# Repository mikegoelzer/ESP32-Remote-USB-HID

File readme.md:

# USB HID Keyboard over Wifi

This project is the hardware and firmware for an ESP32-based remote USB keyboard. It's a dongle that plugs into a USB port on a computer and sends keystrokes that it receives over Wifi.  The connector `J3` also allows for wiring up to the PC motherboard's `F_PANEL` control pins, allowing for remote on/off and remote reboot.  

If you run a JST 4-conductor wire to `F_PANEL` there is a small adapter PCB that plugs it into the motherboard connector.

## Hardware

There are two Kicad projects, one for the USB key and one for the small adapter PCB:

  - USB keyboard PCB
    - [Schematic](Schematics/USBHIDKey.pdf)
    - [`USBHIDKey`](USBHIDKey/)
  - Adapter PCB
    - [Schematic](Schematics/F_PANEL_Shim.pdf)
    - [`F_PANEL_Adapter`](F_PANEL_Adapter/)

## Firmware

The firmware is in the [`esp32-firmware`](esp32-firmware/) directory. See its [README](esp32-firmware/usb-hid-kybd/README.md) for details.

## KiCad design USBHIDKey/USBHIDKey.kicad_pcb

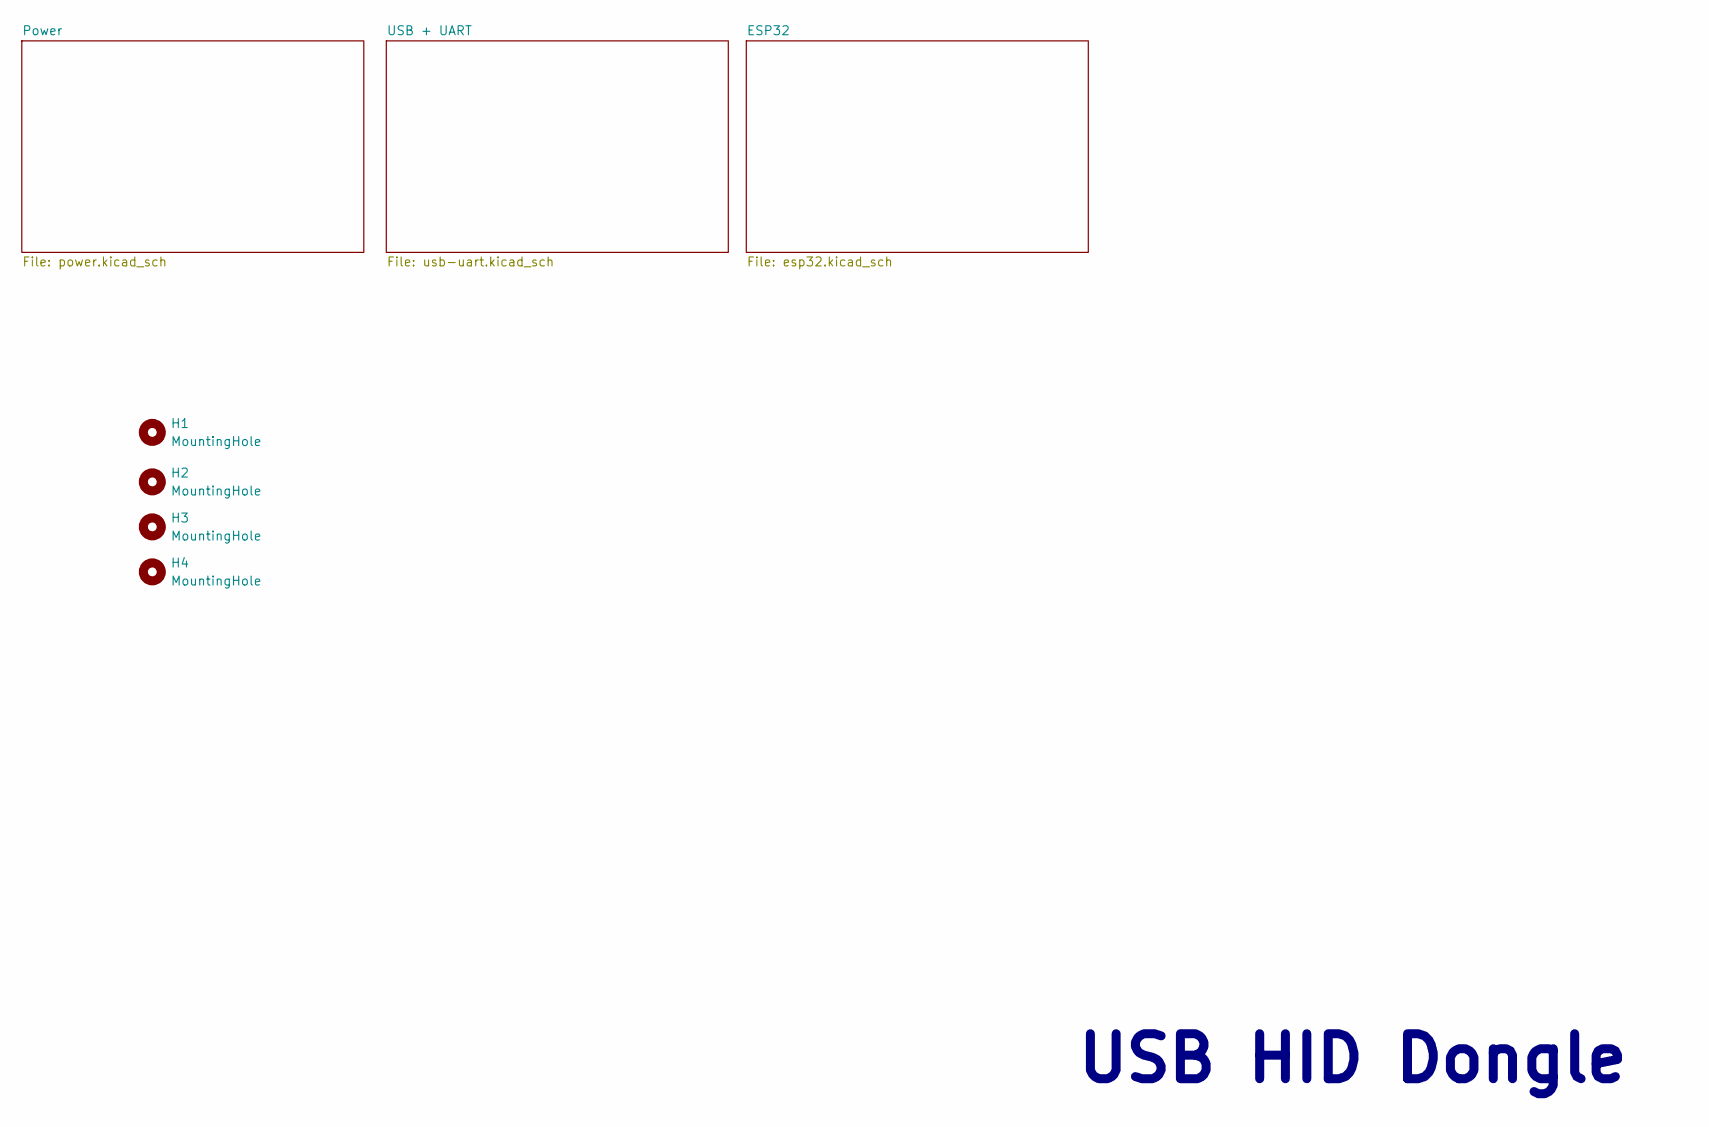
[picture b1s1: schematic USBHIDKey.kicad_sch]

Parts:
H1, H2, H3, H4: MountingHole; MountingHole_3mm

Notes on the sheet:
USB HID Dongle

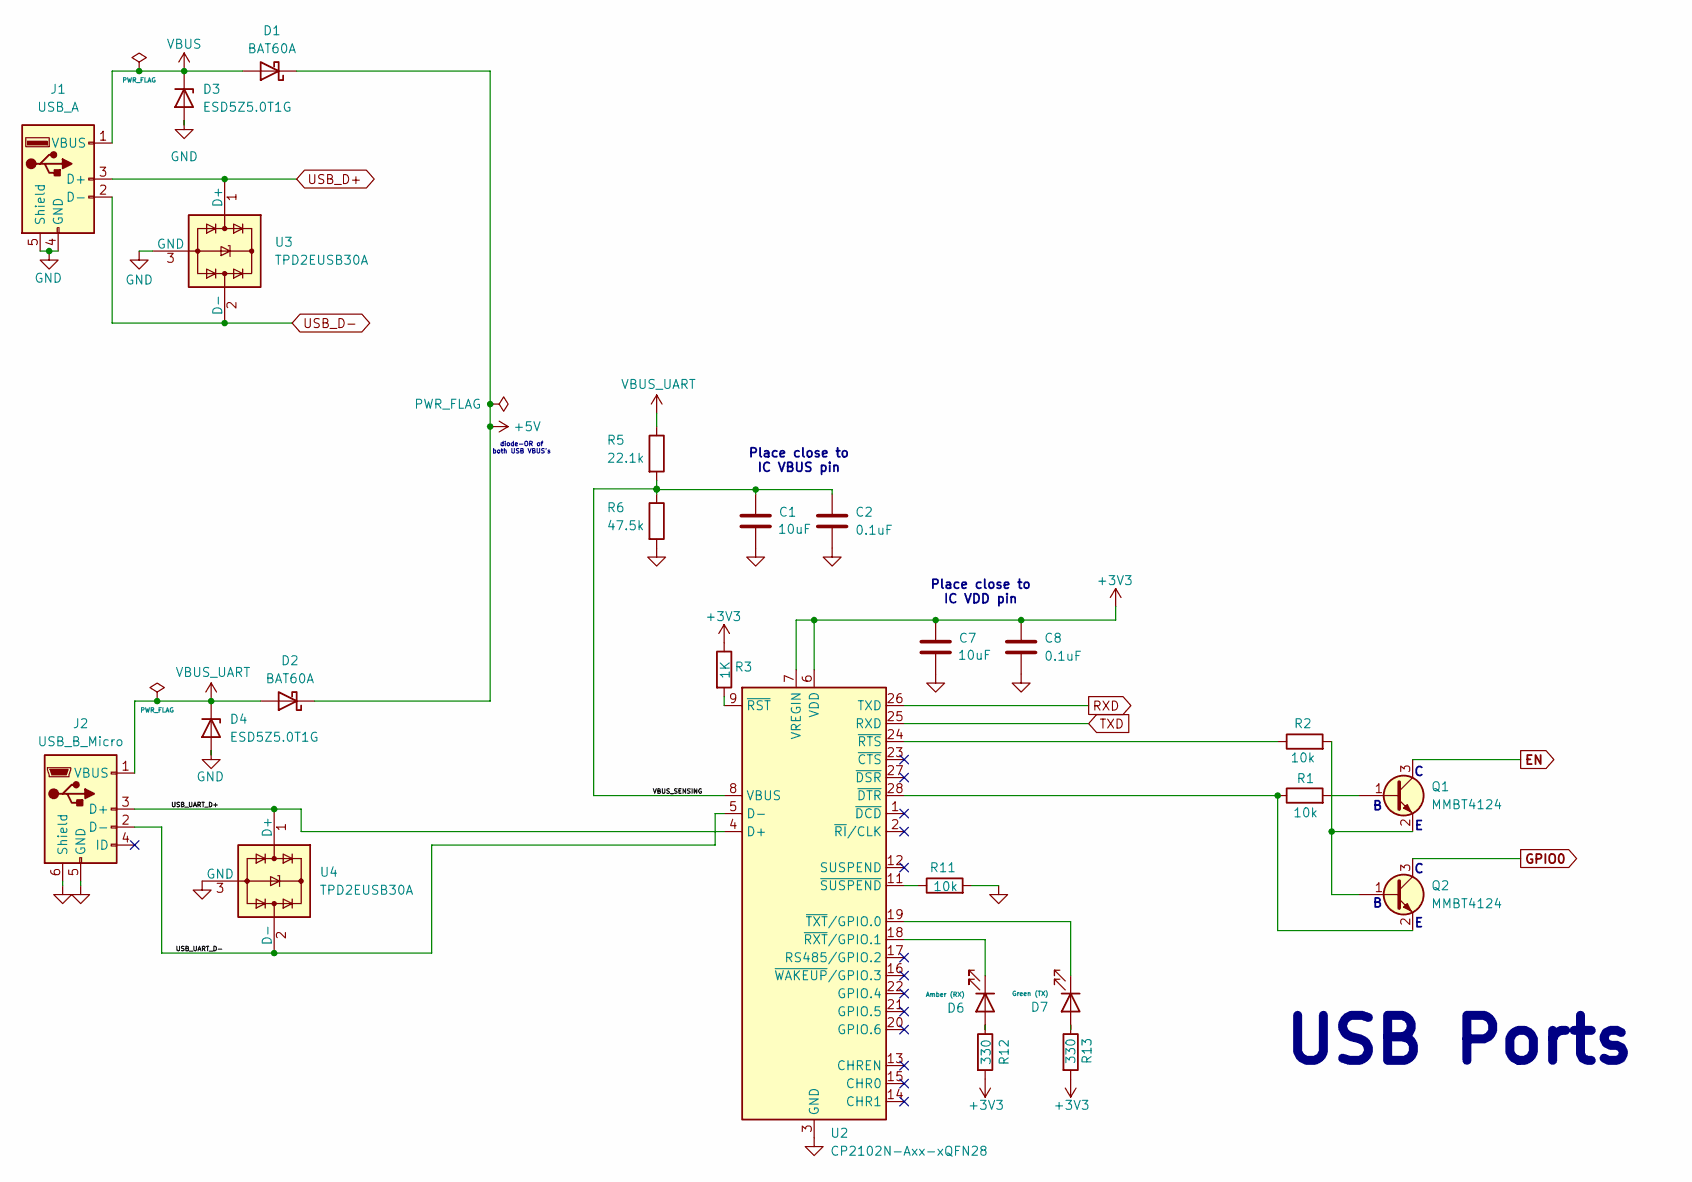
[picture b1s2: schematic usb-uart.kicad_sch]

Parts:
C1, C7: 10uF; C_0603_1608Metric; MPN GRM188Z71A106KA73D
C2, C8: 0.1uF; C_0603_1608Metric; MPN GRM188R72A104KA35D
D1, D2: BAT60A; D_SOD-323; MPN BAT60AE6327HTSA1
D3, D4: ESD5Z5.0T1G; D_SOD-523; MPN ESD5Z5.0T1G
D6: Amber (RX); LED_0603_1608Metric; MPN 150060AS75000
D7: Green (TX); LED_0603_1608Metric; MPN 150060VS75000
J1: USB_A; USB_A_Molex_48037-2200_Horizontal; MPN 0480372200
J2: USB_B_Micro; USB_Micro-B_Amphenol_10118193-0001LF_Horizontal; MPN 10118193-0001LF
Q1, Q2: MMBT4124; SOT-23; MPN MMBT4124LT1G
R1, R2, R11: 10k; R_0201_0603Metric; MPN RC0201FR-0710KL
R3: 1K; R_0201_0603Metric; MPN RC0201FR-071KL
R5: 22.1k; R_0201_0603Metric; MPN ERJ-1GNF2212C
R6: 47.5k; R_0201_0603Metric; MPN ERJ-1GNF4752C
R12, R13: 330; R_0201_0603Metric; MPN RC0201FR-07330KL
U2: CP2102N-Axx-xQFN28; QFN-28-1EP_5x5mm_P0.5mm_EP3.35x3.35mm; MPN CP2102N-A02-GQFN28
U3, U4: TPD2EUSB30A; Texas_DRT-3; MPN TPD2EUSB30ADRTR

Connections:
+3V3: C7.1, C8.1, R3.1, R12.2, R13.2, U2.6 (VDD), U2.7 (VREGIN); also elsewhere on the board
+5V: D1.1 (K), D2.1 (K); also elsewhere on the board
/USB + UART/USB_UART_D+: J2.3 (D+), U2.4 (D+), U4.1 (D+)
/USB + UART/USB_UART_D-: J2.2 (D-), U2.5 (D-), U4.2 (D-)
/USB + UART/VBUS_SENSING: C1.1, C2.1, R5.2, R6.1, U2.8 (VBUS)
EN: Q1.3 (C); also elsewhere on the board
GND: C1.2, C2.2, C7.2, C8.2, D3.2 (A), D4.2 (A), J1.4 (GND), J1.5 (Shield), J2.5 (GND), J2.6 (Shield), R6.2, R11.2, U2.3 (GND), U2.29 (GND), U3.3 (GND), U4.3 (GND); also elsewhere on the board
GPIO0: Q2.3 (C); also elsewhere on the board
unnamed: D6.2 (A), R12.1
unnamed: D6.1 (K), U2.18 (~RXT/GPIO.1)
unnamed: D7.2 (A), R13.1
unnamed: D7.1 (K), U2.19 (~TXT/GPIO.0)
unnamed: Q1.1 (B), R1.2
unnamed: Q1.2 (E), Q2.1 (B), R2.2
unnamed: Q2.2 (E), R1.1, U2.28 (~DTR)
unnamed: R3.2, U2.9 (~RST)
unnamed: R2.1, U2.24 (~RTS)
unnamed: R11.1, U2.11 (~SUSPEND)
RXD: U2.26 (TXD); also elsewhere on the board
TXD: U2.25 (RXD); also elsewhere on the board
USB_D+: J1.3 (D+), U3.1 (D+); also elsewhere on the board
USB_D-: J1.2 (D-), U3.2 (D-); also elsewhere on the board
VBUS: D1.2 (A), D3.1 (K), J1.1 (VBUS)
VBUS_UART: D2.2 (A), D4.1 (K), J2.1 (VBUS), R5.1

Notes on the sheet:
Place close to IC VDD pin
diode-OR of both USB VBUS's
Place close to IC VBUS pin
USB Ports

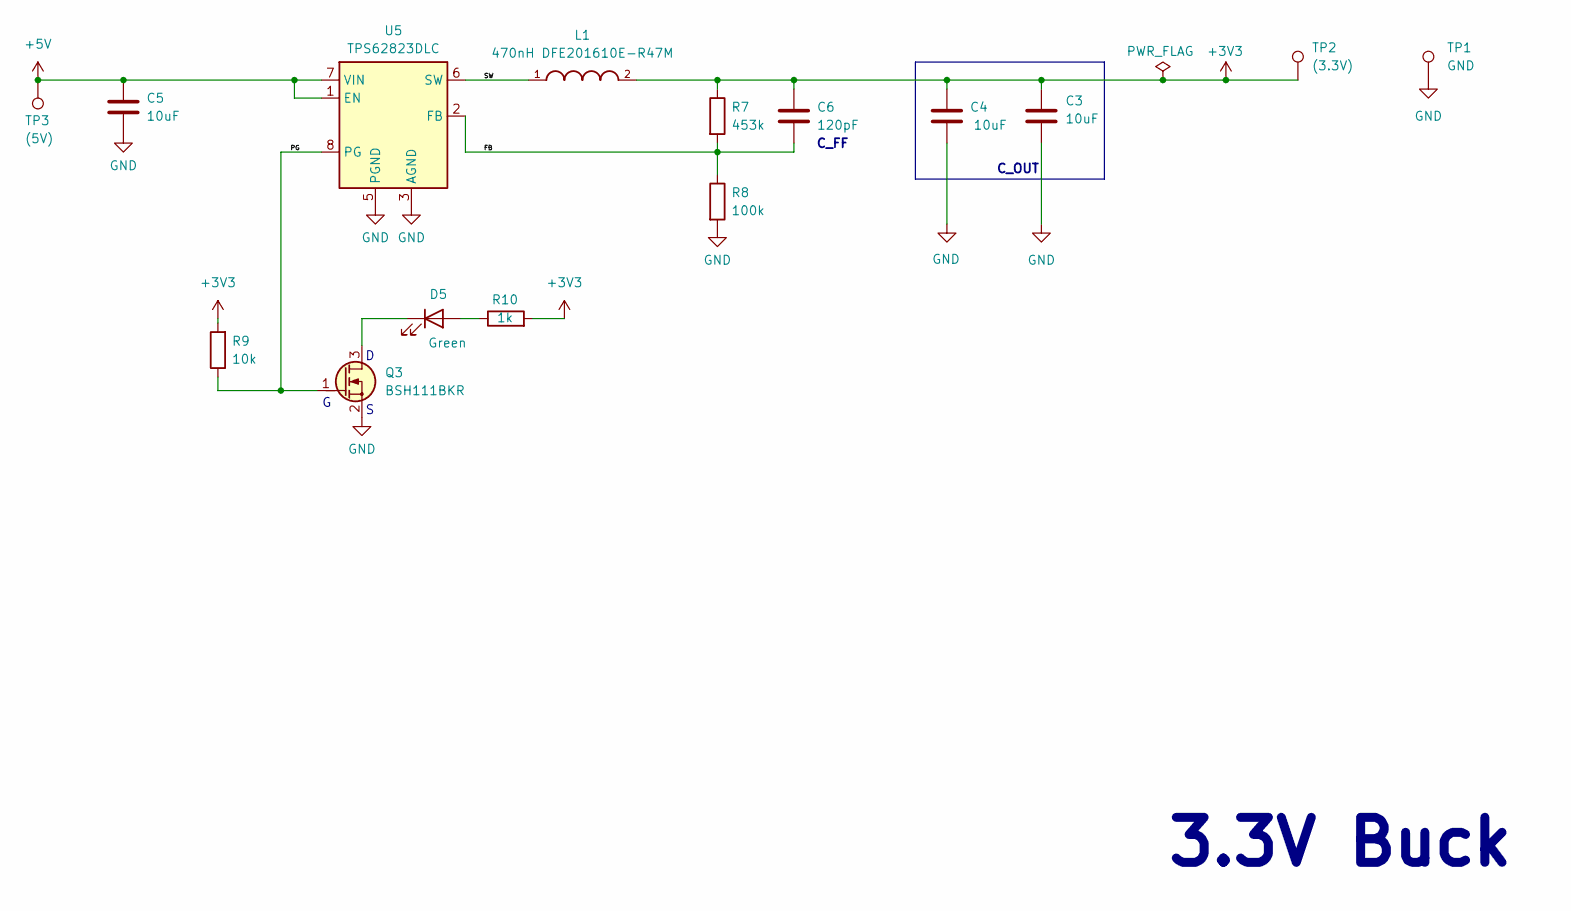
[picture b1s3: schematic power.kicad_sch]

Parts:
C3, C4, C5: 10uF; C_0603_1608Metric; MPN GRM188Z71A106KA73D
C6: 120pF; C_0201_0603Metric; MPN GRM033R71E121KA01D
D5: Green; LED_0603_1608Metric; MPN 150060VS75000
L1: 470nH DFE201610E-R47M; DFE201610E-R47M=P2; MPN DFE201610E-R47M=P2
Q3: BSH111BKR; SOT-23; MPN BSH111BKR
R7: 453k; R_0201_0603Metric; MPN RC0201FR-07453KL
R8: 100k; R_0201_0603Metric; MPN RC0201FR-07100KL
R9: 10k; R_0201_0603Metric; MPN RC0201FR-0710KL
R10: 1k; R_0201_0603Metric; MPN RC0201FR-071KL
TP1: GND; TestPoint_Pad_2.0x2.0mm
TP2: (3.3V); TestPoint_Pad_2.0x2.0mm
TP3: (5V); TestPoint_Pad_2.0x2.0mm
U5: TPS62823DLC; Texas_VSON-HR-8_1.5x2mm_P0.5mm; MPN TPS62823DLCT

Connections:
+3V3: C3.1, C4.1, C6.1, L1.2, R7.1, R9.2, R10.2, TP2.1; also elsewhere on the board
+5V: C5.1, TP3.1, U5.1 (EN), U5.7 (VIN); also elsewhere on the board
/Power/FB: C6.2, R7.2, R8.1, U5.2 (FB)
/Power/PG: Q3.1 (G), R9.1, U5.8 (PG)
/Power/SW: L1.1, U5.6 (SW)
GND: C3.2, C4.2, C5.2, Q3.2 (S), R8.2, TP1.1, U5.3 (AGND), U5.5 (PGND); also elsewhere on the board
unnamed: D5.2 (A), R10.1
unnamed: D5.1 (K), Q3.3 (D)

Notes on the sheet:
3.3V Buck
C_FF
C_OUT

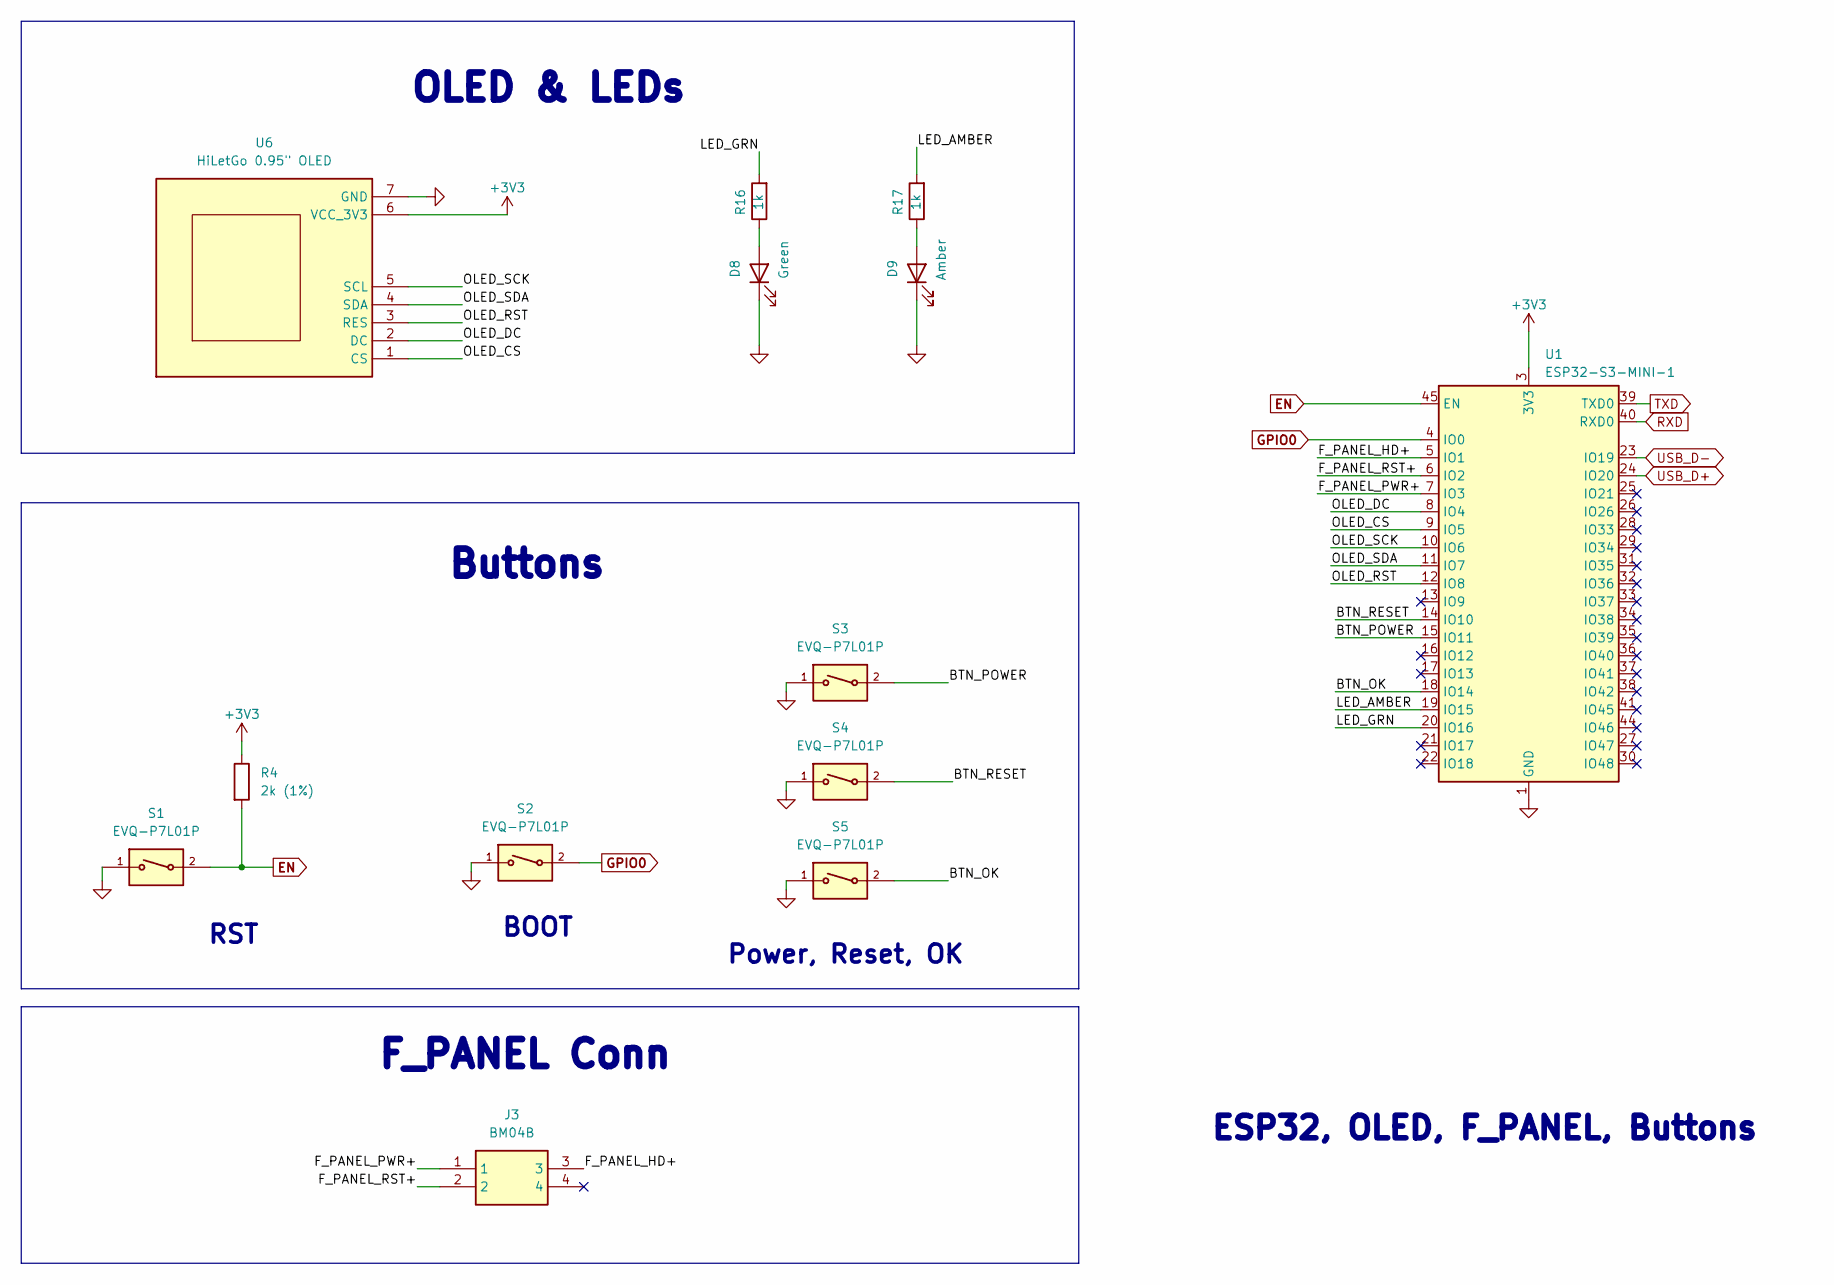
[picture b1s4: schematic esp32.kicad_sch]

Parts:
D8: Green; LED_0603_1608Metric; MPN 150060VS75000
D9: Amber; LED_0603_1608Metric; MPN 150060AS75000
J3: BM04B; BM04B-SRSS-TB_LFSN_; MPN BM04B-SRSS-TB(LF)(SN)
R4: 2k (1%); R_0201_0603Metric; MPN RC0201FR-072KL
R16, R17: 1k; R_0201_0603Metric; MPN RC0201FR-071KL
S1, S2, S3, S4, S5: EVQ-P7L01P; SW_EVQ-P7L01P; MPN EVQ-P7L01P
U1: ESP32-S3-MINI-1; ESP32-S2-MINI-1; MPN ESP32-S3-MINI-1-N8
U6: HiLetGo 0.95" OLED; OLED 0.95in Receptacle+Holes Only Footprint

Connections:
+3V3: R4.1, U1.3 (3V3), U6.6 (VCC_3V3); also elsewhere on the board
/ESP32/BTN_OK: S5.2, U1.18 (IO14)
/ESP32/BTN_POWER: S3.2, U1.15 (IO11)
/ESP32/BTN_RESET: S4.2, U1.14 (IO10)
/ESP32/F_PANEL_HD+: J3.3, U1.5 (IO1)
/ESP32/F_PANEL_PWR+: J3.1, U1.7 (IO3)
/ESP32/F_PANEL_RST+: J3.2, U1.6 (IO2)
/ESP32/LED_AMBER: R17.2, U1.19 (IO15)
/ESP32/LED_GRN: R16.2, U1.20 (IO16)
/ESP32/OLED_CS: U1.9 (IO5), U6.1 (CS)
/ESP32/OLED_DC: U1.8 (IO4), U6.2 (DC)
/ESP32/OLED_RST: U1.12 (IO8), U6.3 (RES)
/ESP32/OLED_SCK: U1.10 (IO6), U6.5 (SCL)
/ESP32/OLED_SDA: U1.11 (IO7), U6.4 (SDA)
EN: R4.2, S1.2, U1.45 (EN); also elsewhere on the board
GND: D8.1 (K), D9.1 (K), S1.1, S2.1, S3.1, S4.1, S5.1, U1.1 (GND), U1.2 (GND), U1.42 (GND), U1.43 (GND), U1.46 (GND), U1.47 (GND), U1.48 (GND), U1.49 (GND), U1.50 (GND), U1.51 (GND), U1.52 (GND), U1.53 (GND), U1.54 (GND), U1.55 (GND), U1.56 (GND), U1.57 (GND), U1.58 (GND), U1.59 (GND), U1.60 (GND), U1.61 (GND), U1.62 (GND), U1.63 (GND), U1.64 (GND), U1.65 (GND), U6.7 (GND); also elsewhere on the board
GPIO0: S2.2, U1.4 (IO0); also elsewhere on the board
unnamed: D8.2 (A), R16.1
unnamed: D9.2 (A), R17.1
RXD: U1.40 (RXD0); also elsewhere on the board
TXD: U1.39 (TXD0); also elsewhere on the board
USB_D+: U1.24 (IO20); also elsewhere on the board
USB_D-: U1.23 (IO19); also elsewhere on the board

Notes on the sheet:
Power, Reset, OK
RST
OLED & LEDs
Buttons
BOOT
F_PANEL Conn
ESP32, OLED, F_PANEL, Buttons

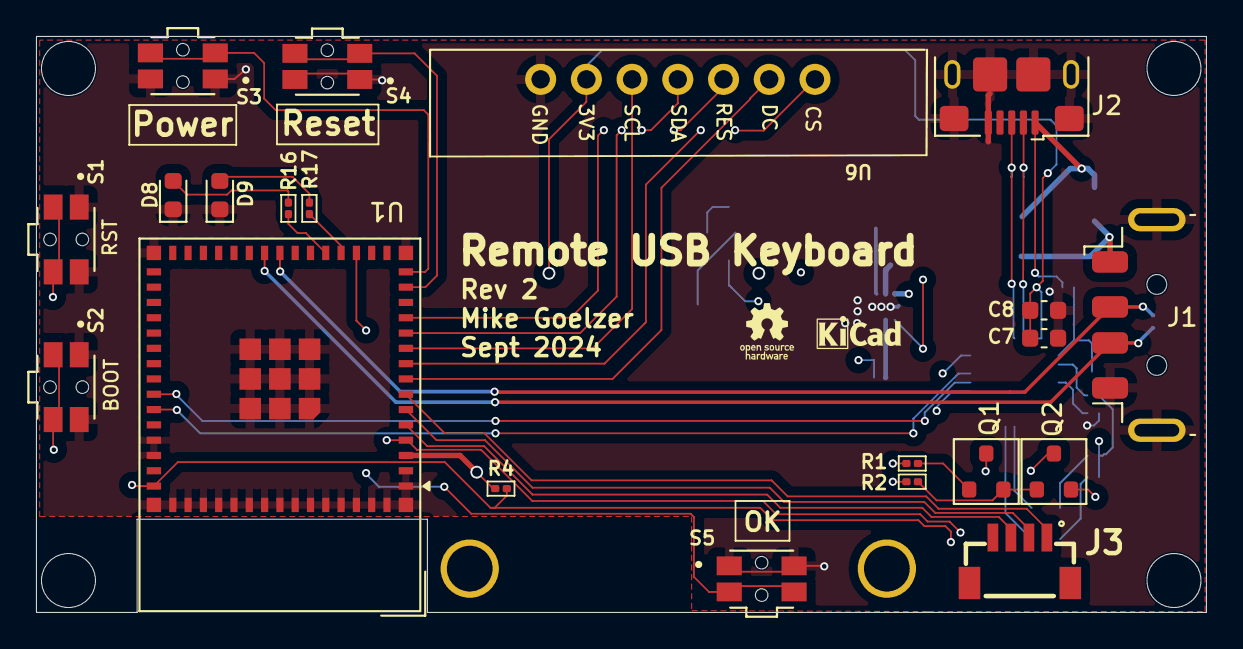
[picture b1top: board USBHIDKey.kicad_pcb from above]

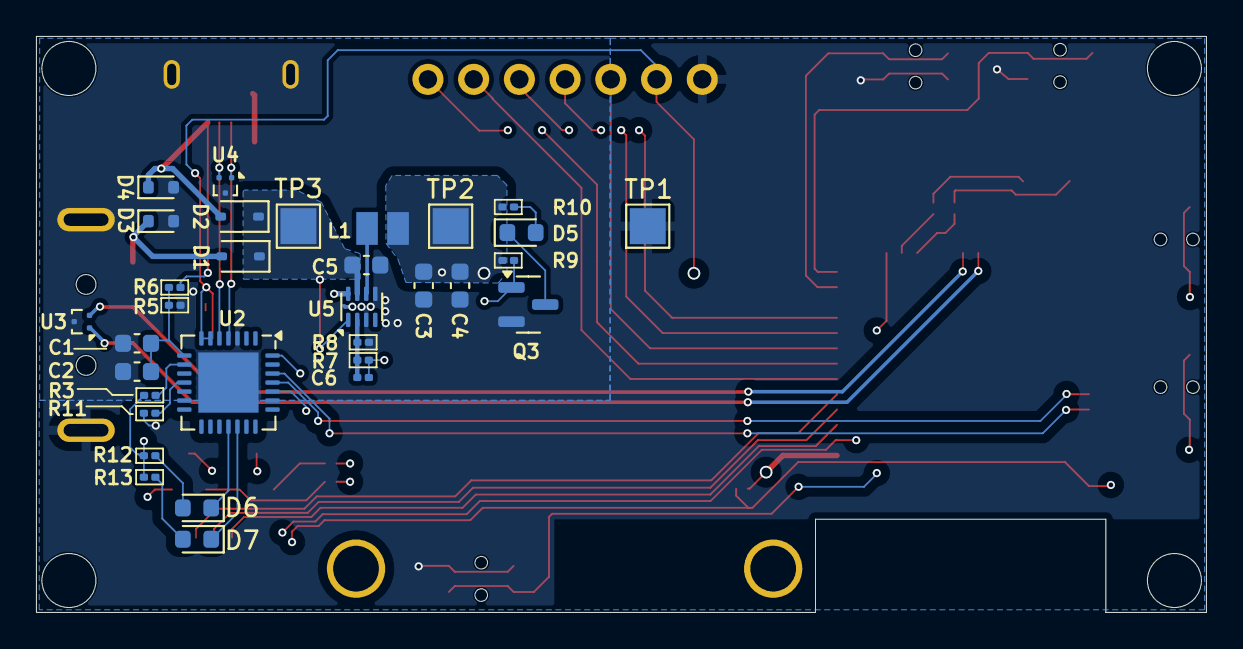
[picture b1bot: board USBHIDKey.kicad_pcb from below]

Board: 4 copper layers, 65.0 x 32.0 mm, 57 parts (32 on the bottom side), 44 nets.

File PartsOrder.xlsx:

Desc | Part Ref |  | Actual Qty | Order Qty | Price | Subtotal | In basket? | Ordered? | Mfgr | MPN | Vendor URL | LCSC URL | Notes |  | Digikey | Adafruit | Mouser | Sparkfun
F_PANEL Shim | # of boards |  | 3
TSM-110-02-L-DH (2x10 RA male header 0.1") | J3 |  | 1 | 3 | 3.04 | 9.120000000000001 | ✅ | ❌ |  |  | https://www.digikey.com/en/products/detail/samtec-inc/TSM-11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 |  |  |  | 1
SMH-110-02-L-D (2x10 RA female receptacle 0.1") | J2 |  | 1 | 3 | 3.97 | 11.91 | ✅ | ❌ |  |  | https://www.digikey.com/en/products/detail/samtec-inc/SMH-11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
PRT-17257 - 18" JST SH male-male cable |  |  | 1 | 1 | 2.38 | 2.38 | ✅ | ❌ |  |  | https://www.digikey.com/en/products/detail/sparkfun-electron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
BM04B-SRSS-TB female vertical JST SH SMT receptacle | J1 |  | 1 | 3 | 0.62 | 1.8599999999999999 | ✅ | ❌ |  |  | https://www.digikey.com/en/products/detail/jst-sales-america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
USB Dongle | # of boards |  | 3
CP2102N | U2 |  | 1 | 3 | 4.66 | 13.98 | - | - | Silicon Labs | CP2102N-A02-GQFN28 | https://www.digikey.com/en/products/detail/silicon-labs/CP21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 | https://www.lcsc.com/product-detail/USB-Converters_SKYWORKS-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 |  |  | 1
ESP32-S3-MINI-1-N8 | U1 |  | 1 | 3 | 3.1 | 9.3000000000000007 | - | - | Expressif | ESP32-S3-MINI-1-N8 | https://www.digikey.com/en/products/detail/espressif-systems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 | https://www.lcsc.com/product-detail/WiFi-Modules_Espressif-S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
MMBT4124LT1G (NPN BJT in SOT-23) | Q1,Q2 |  | 2 | 6 | 0.2 | 1.2000000000000002 | - | - | onsemi | MMBT4124LT1G | https://www.digikey.com/en/products/detail/onsemi/MMBT4124LT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
resistor 10k 1% 0201 | R1,R2,R9,R11 |  | 4 | 12 | 0.1 | 1.2000000000000002 | - | - | YAGEO | RC0201FR-0710KL | https://www.digikey.com/en/products/detail/yageo/RC0201FR-07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
resistor 1k 1% 0201 | R3,R10,R12,R13,R16,R17 |  | 6 | 18 | 0.1 | 1.8 | - | - | YAGEO | RC0201FR-071KL | https://www.digikey.com/en/products/detail/yageo/RC0201FR-07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
resistor 2k 1% 0201 | R4 |  | 1 | 3 | 0.1 | 0.30000000000000004 | - | - | YAGEO | RC0201FR-072KL | https://www.digikey.com/en/products/detail/yageo/RC0201FR-07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
resistor 22.1K 1% 0201 | R5 |  | 1 | 3 | 0.1 | 0.30000000000000004 | - | - | Panasonic | ERJ-1GNF2212C | https://www.digikey.com/en/products/detail/panasonic-electro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
resistor 47.5K 1% 0201 | R6 |  | 1 | 3 | 0 | 0 | - | - | Panasonic | ERJ-1GNF4752C | https://www.digikey.com/en/products/detail/panasonic-electro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
resistor 100k 1% 0201 | R7 |  | 1 | 3 | 0.1 | 0.30000000000000004 | - | - | YAGEO | RC0201FR-07100KL | https://www.digikey.com/en/products/detail/yageo/RC0201FR-07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
resistor 453k 1% 0201 | R8 |  | 1 | 3 | 0.1 | 0.30000000000000004 | - | - | YAGEO | RC0201FR-07453KL | https://www.digikey.com/en/products/detail/yageo/RC0201FR-07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
cap X7R 10uF/16V (10%) 0603 | C1, C3, C4, C5, C7 |  | 5 | 15 | 0.33 | 4.95 | - | - | MuRata | GRM188Z71A106KA73D | https://www.digikey.com/en/products/detail/murata-electronic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 |  |  |  | 1
cap X7R 0.1uF/100V (10%) 0603 | C2, C8 |  | 2 | 6 | 0.21 | 1.26 | - | - | MuRata | GRM188R72A104KA35D | https://www.digikey.com/en/products/detail/murata-electronic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 |  |  |  | 1
CAP CER 120PF 25V X7R 0201 | C6 |  | 1 | 3 | 0.1 | 0.30000000000000004 | - | - | MuRata | GRM033R71E121KA01D | https://www.digikey.com/en/products/detail/murata-electronic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
TPD2EUSB30A bidir D+/D- TVs in TI DRT-3 (SOT-23-3) | U3,U4 |  | 2 | 6 | 0.48 | 2.88 | - | - | TI | TPD2EUSB30ADRTR | https://www.digikey.com/en/products/detail/texas-instruments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 |  |  |  | 1
ESD5Z5.0T1G TVS diode, undirectional, in SOD-523 | D1,D2 |  | 2 | 6 | 0.24 | 1.44 | - | - | onsemi | ESD5Z5.0T1G | https://www.digikey.com/en/products/detail/onsemi/ESD5Z5-0T1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 |  |  |  | 1
BAT60A Schottky 3A/10V in SOD-323 | D3,D4 |  | 2 | 6 | 0.44 | 2.64 | - | - | Infineon | BAT60AE6327HTSA1 | https://www.digikey.com/en/products/detail/infineon-technolo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 |  |  |  | 1
Amphenol 10118193-0001 USB Micro B R/A conn SMT | J2 |  | 1 | 3 | 0.46 | 1.3800000000000001 | - | - | Amphenol | 10118193-0001LF | https://www.digikey.com/en/products/detail/amphenol-cs-fci/1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 |  |  |  | 1
Molex USB-A plug male SMT | J1 |  | 1 | 3 | 1.45 | 4.3499999999999996 | - | - | Molex | 480372200 | https://www.digikey.com/en/products/detail/molex/0480372200/2421361
TPS62823 3A buck | U5 |  | 1 | 3 | 1.93 | 5.79 | - | - | Texas Instruments | TPS62823DLCT | https://www.digikey.com/en/products/detail/texas-instruments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
470nF inductor | L1 |  | 1 | 3 | 0.32 | 0.96 | - | - | MuRata | DFE201610E-R47M=P2 | https://www.digikey.com/en/products/detail/murata-electronic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
N-channel enhancement mode MOSFET BSH111 | Q3 |  | 1 | 3 | 0.26 | 0.78 | - | - | Nexperia | BSH111BKR | https://www.digikey.com/en/products/detail/nexperia-usa-inc/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
Green LED 0603 | D5,D7,D8 |  | 3 | 9 | 0.15 | 1.3499999999999999 | - | - | Wurth | 150060VS75000 | https://www.digikey.com/en/products/detail/w%C3%BCrth-elektr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
Blue LED 0603 |  |  | 1 | 3 | 0.16 | 0.48 | - | - | Wurth | 150060BS75000 | https://www.digikey.com/en/products/detail/w%C3%BCrth-elektr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
Amber LED 0603 | D6,D9 |  | 2 | 6 | 0.15 | 0.89999999999999991 | - | - | Wurth | 150060AS75000 | https://www.digikey.com/en/products/detail/w%C3%BCrth-elektr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
Red LED 0603 |  |  |  | 0 | 0.15 | 0 | - | - | Wurth | 150060SS75000 | https://www.digikey.com/en/products/detail/w%C3%BCrth-elektr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
JST SH series vertical receptacle BM04B | J3 |  | 1 | 3 | 0.62 | 1.8599999999999999 | - | - | JST | BM04B-SRSS-TB | https://www.digikey.com/en/products/detail/jst-sales-america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
HiLetGo 0.95" SPI OLED | U6 |  | 1 | 3 | 12.99 | 38.97 | ❌ | ❌ | HiLetGo | N/A | https://www.amazon.com/dp/B0711RKXB5?psc=1&ref=ppx_yo2ov_dt_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
Right angle SMT tactile button | S1,S2,S3,S4,S5 |  | 4 | 12 | 0.3 | 3.5999999999999996 | - | - | Panasonic | EVQ-P7L01P | https://www.digikey.com/en/products/detail/panasonic-electro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
CONN HDR 7POS 0.1 TIN PCB | U6 |  | 1 | 3 | 0.6 | 1.7999999999999998 | ✅ | ❌ | Sullins | PPTC071LFBN-RC | https://www.digikey.com/en/products/detail/sullins-connector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
Wire
28 AWG wire
PAD-11 crimp tool
22 guage wire (for breadboard, not req'd here)
heat shrink tubing - 24 in?

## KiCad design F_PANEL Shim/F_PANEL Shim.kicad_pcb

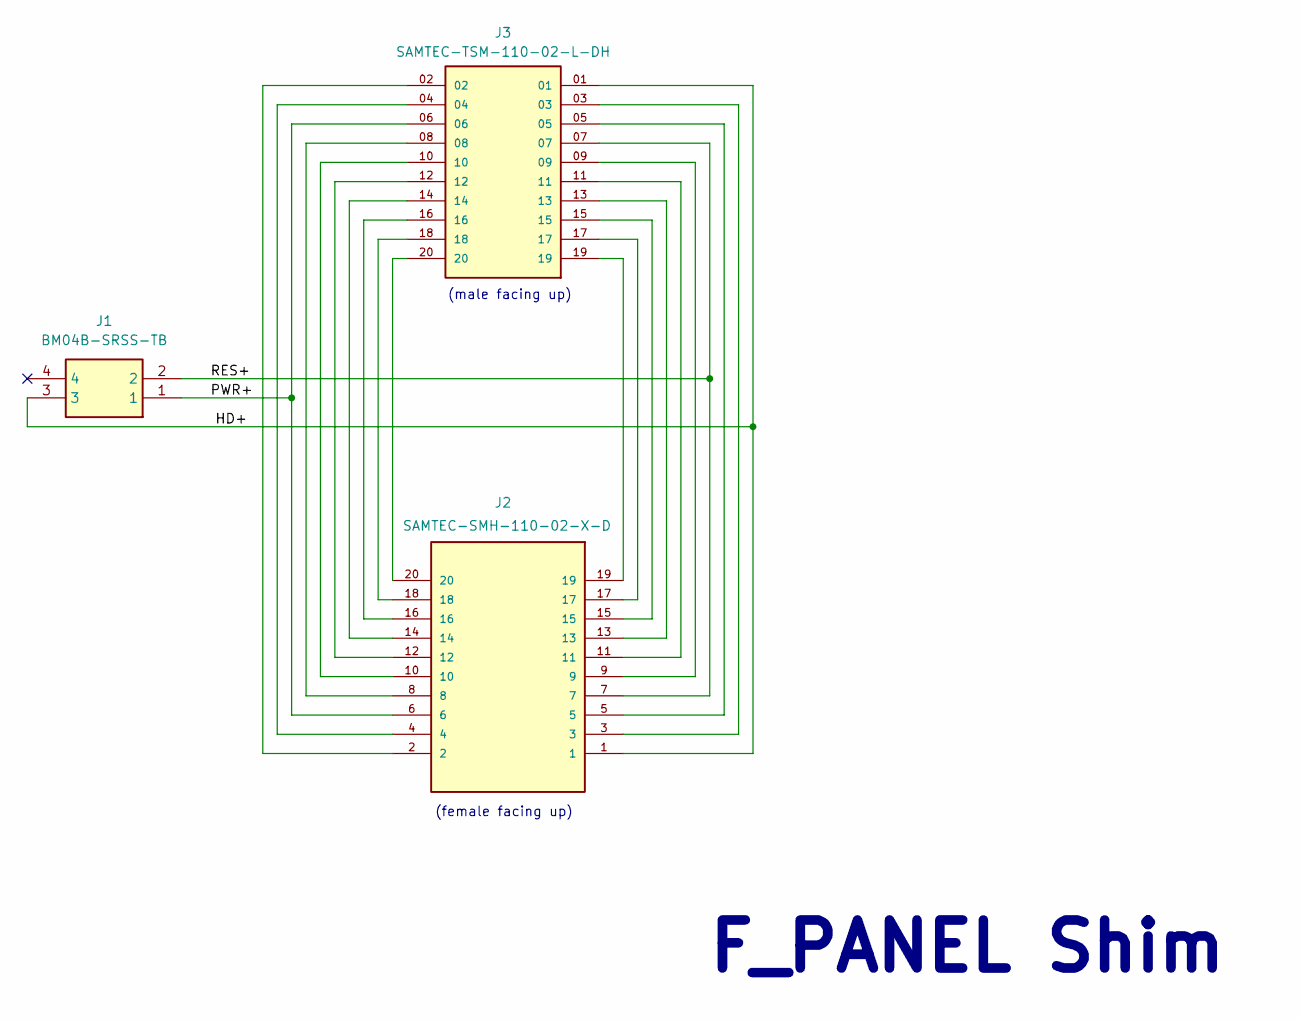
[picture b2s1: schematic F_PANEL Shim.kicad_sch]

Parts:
J1: BM04B-SRSS-TB; JST SH - BM04B-SRSS-TB_LFSN_; Manufacturer_Part_Number BM04B-SRSS-TB(LF)(SN)
J2: SAMTEC-SMH-110-02-X-D
J3: SAMTEC-TSM-110-02-L-DH; SAMTEC_TSM-110-02-L-DH; PARTREV R

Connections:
/HD+: J1.3, J2.1, J3.01
/PWR+: J1.1, J2.6, J3.06
/RES+: J1.2, J2.7, J3.07
unnamed: J2.2, J3.02
unnamed: J2.3, J3.03
unnamed: J2.4, J3.04
unnamed: J2.5, J3.05
unnamed: J2.8, J3.08
unnamed: J2.9, J3.09
unnamed: J2.10, J3.10
unnamed: J2.11, J3.11
unnamed: J2.12, J3.12
unnamed: J2.13, J3.13
unnamed: J2.14, J3.14
unnamed: J2.15, J3.15
unnamed: J2.16, J3.16
unnamed: J2.17, J3.17
unnamed: J2.18, J3.18
unnamed: J2.19, J3.19
unnamed: J2.20, J3.20

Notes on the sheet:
F_PANEL Shim
(male facing up)
(female facing up)

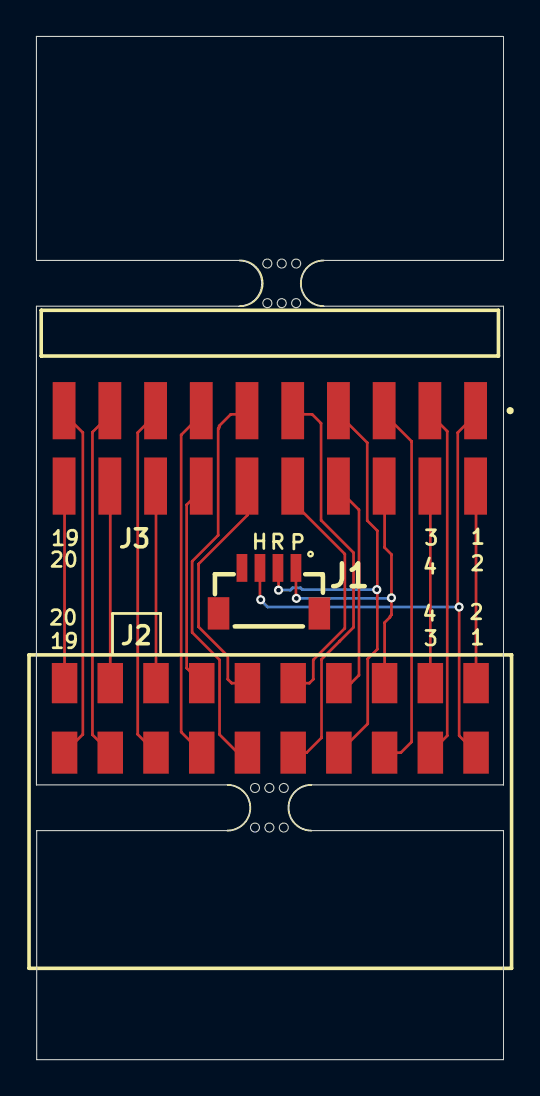
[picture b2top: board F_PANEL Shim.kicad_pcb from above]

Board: 2 copper layers, 25.9 x 56.8 mm, 5 parts (0 on the bottom side), 20 nets.

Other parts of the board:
mouse-bite-2.54mm-slot, mouse-bite-2.54mm-slot#2: VAL**; mouse-bite-2.54mm-slot

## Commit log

2024-07-16 relocate workspace file
2024-07-16 relocate esp32 firmware
2024-07-16 dir rename
2024-07-16 silkscreen images and readme
2024-07-16 add silkscreen images in kicad
2024-07-16 renames and temp files
2024-07-16 file rename
2024-07-16 backup files
2024-07-16 remove backup zip files
2024-07-16 add backup zip files to gitigonore
2024-07-16 script for bulk modify pcb parts
2024-07-16 fix 3d models for some parts
2024-07-16 Fix up project's readme
2024-07-16 rename usb keyboard 3d render image
2024-07-16 remove old ignored backup
2024-07-16 silkscreen fix
2024-07-23 updates for PCBWay assembly order
2024-07-23 vscode workspace
2024-07-23 move workspace file to top level
2024-09-06 update ignores
2024-09-06 backup zips now ignored
2024-09-06 Remove tracked files that should be ignored
2024-09-06 update gitignore
2024-09-08 get kicad auto-backup files out of git's index
2024-09-08 feedback resistor calcs for tps62283
2024-09-08 BOM changes: moved original to rev1 dir; started new BOM in rev2 dir
2024-09-08 renamed rev2 bom for clarity
2024-09-08 fix excel extension so file opens in Excel
2024-09-08 fixes #5
2024-09-08 remove useless DNP rows from bom
2024-09-08 change TX/RX LED resistors to 330
2024-09-08 correct R12/R13 pads to 0603 on pcd; fix ERC errors relating to Kicad library update
2024-09-08 swap values of R7/R8 to fix buck Vout
2024-09-08 swap R7/R8 resistor values in BOM
2024-09-08 correct D6/D7 on BOM since now correct on pcb
2024-09-08 specify exact resistor part numbers in BOM xls
2024-09-08 regenerate gerbers
2024-09-08 update DRC ignores after checking
2024-09-08 moved vscode workspace file into scripts dir
2024-09-08 update silk to 'rev 2'
2024-10-30 update instructions for ESP32-S3
2024-10-30 set workspace file types
2024-10-30 reduce red squiggles in cursor with hardcoded ESP-IDF paths
2024-10-30 add tinyusb component + docs update buold instructions in README
2024-11-07 ESP-IDF USB code (non-working)
2024-11-07 add explanation of USB failure with ESP-IDF version of code
2024-11-07 replace with Arduino version of firmware
